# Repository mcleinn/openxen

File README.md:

# openxen

Custom Hall-effect microtonal hex keyboard: five identical 56-key Lumatone-shaped modules with Wooting Lekker Tikken switches, one AT32F405 per module, analog key depth streamed to [xentool](https://github.com/mcleinn/xentool).

Successor of [freexen](https://github.com/mcleinn/freexen) (DIY printed switches, one Teensy) and of the Wooting/Exquis software-only approach.

- `PROJECT_PLAN.md` — the plan, decisions and gates (read this first)
- `docs/` — our documents (provenance, verification notes, user inputs)
- `layout/` — machine-readable module specification and the generators built on it
- `hardware/` — KiCad project for the module PCB (derived from HE60, GPL-3.0)
- `firmware/` — libhmk-derived firmware for the module (GPL-3.0)
- `host/` — notes for the xentool backend
- `case/` — deltas against the freexen case
- `reference/` — third-party clones, datasheets and photos; **not part of the repository** (see `.gitignore`)

Hardware and firmware derived from [peppapighs/HE60](https://github.com/peppapighs/HE60) and [peppapighs/libhmk](https://github.com/peppapighs/libhmk) are licensed GPL-3.0; see `docs/provenance.md` for pinned commits.

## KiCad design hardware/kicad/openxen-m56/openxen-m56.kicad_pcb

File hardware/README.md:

# hardware — module PCB (KiCad 9)

Derived from HE60 v2.1 (GPL-3.0). Everything here is generated from `layout/module.json`, `parts.json` and HE60's files by the scripts in `generators/`; regenerate rather than hand-edit until Phase 4 routing starts.

| Path | Content |
|---|---|
| `parts.json` | Every part with LCSC code, footprint, JLCPCB basic/extended status and the reason for the choice |
| `kicad/lib/openxen.pretty` | `SW_Lekker_1u`, `LED_RGB_1206R_MHT151RGBCT` |
| `kicad/lib/openxen.kicad_sym` | MT9102ET (pin-compatible with GH39FKSW) and AT32F405RxT7 symbols from HE60 |
| `kicad/openxen-m56/` | project, library tables, generated schematic |
| `generators/sexp.py`, `kicad_sch.py` | S-expression reader/writer and schematic helpers |
| `generators/gen_project.py` | symbol library + project files |
| `generators/gen_schematic.py` | the schematic (run after `gen_project.py`) |

Checks: `kicad-cli sch erc --severity-all` on the schematic (clean as of 2026-11-06, one library-version note on the crystal symbol).

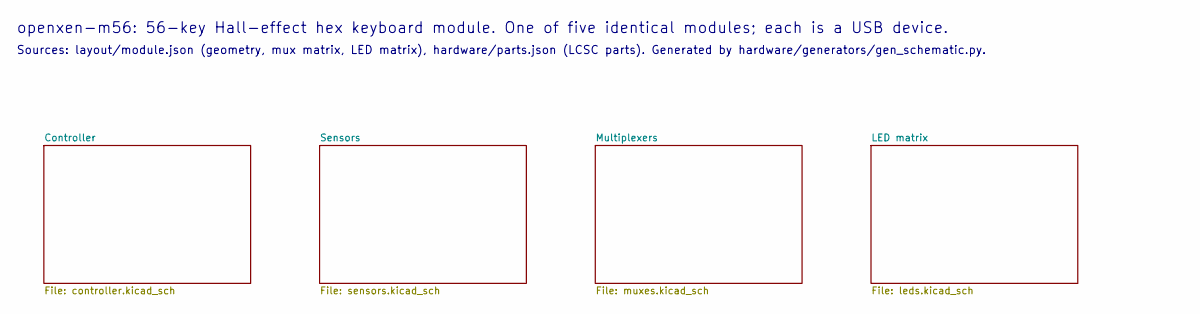
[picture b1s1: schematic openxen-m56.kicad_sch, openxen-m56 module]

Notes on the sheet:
openxen-m56: 56-key Hall-effect hex keyboard module. One of five identical modules; each is a USB device.
Sources: layout/module.json (geometry, mux matrix, LED matrix), hardware/parts.json (LCSC parts). Generated by hardware/generators/gen_schematic.py.

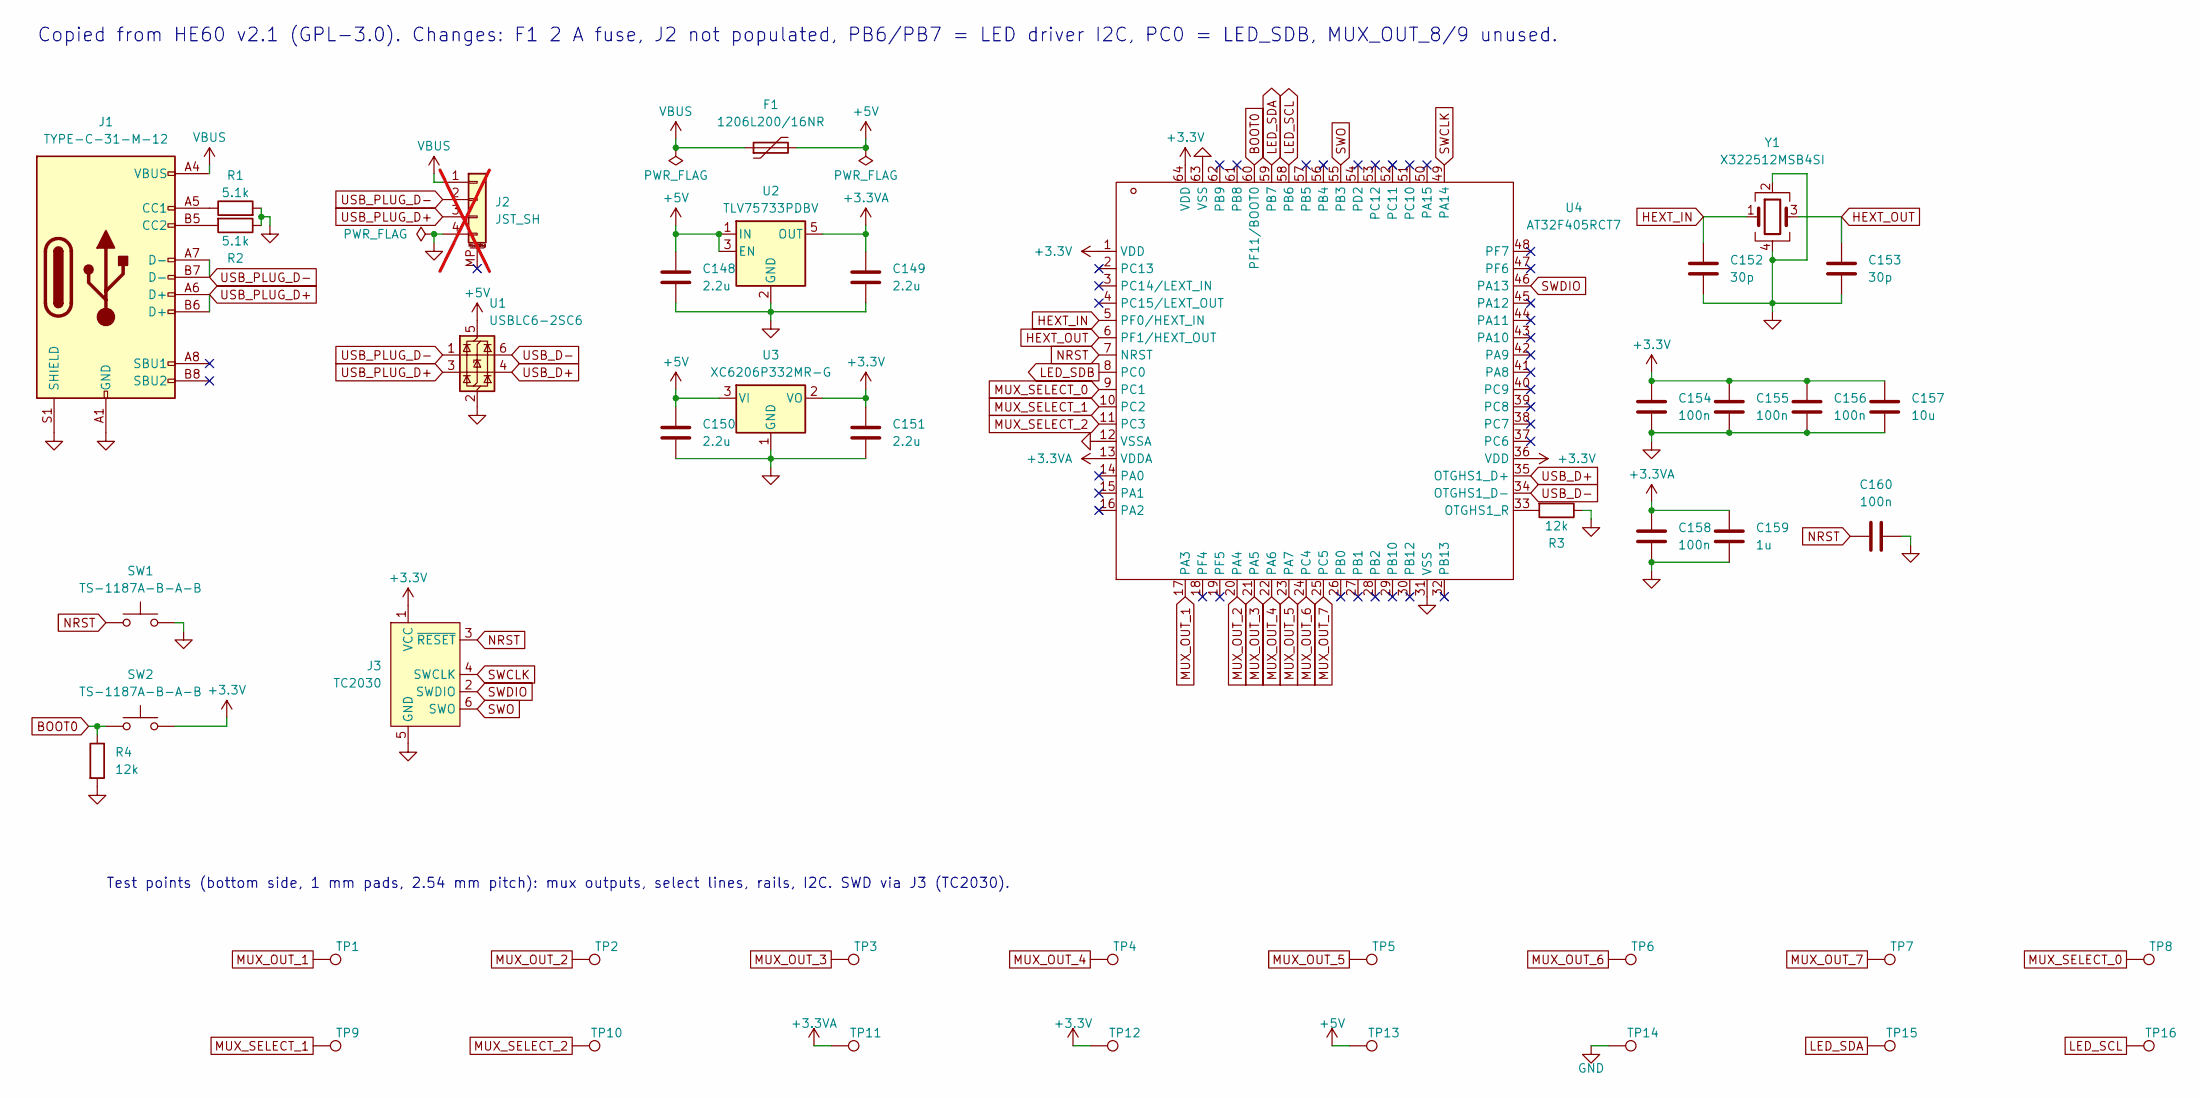
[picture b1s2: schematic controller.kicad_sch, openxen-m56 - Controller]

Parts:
C148, C149, C150, C151: 2.2u; C_0603_1608Metric; MPN CL10A225KO8NNNC; LCSC Part # C23630
C152, C153: 30p; C_0603_1608Metric; MPN 0603CG300J500NT; LCSC Part # C1658
C154, C155, C156, C158, C160: 100n; C_0402_1005Metric; MPN CL05B104KO5NNNC; LCSC Part # C1525
C157: 10u; C_0603_1608Metric; MPN CL10A106KP8NNNC; LCSC Part # C19702
C159: 1u; C_0603_1608Metric; MPN CL10A105KB8NNNC; LCSC Part # C15849
F1: 1206L200/16NR; Fuse_1206_3216Metric; MPN 1206L200/16NR; LCSC Part # C22374899
J1: TYPE-C-31-M-12; USB_C_Receptacle_HRO_TYPE-C-31-M-12; MPN TYPE-C-31-M-12; LCSC Part # C165948
J2: JST_SH; JST_SH_SM04B-SRSS-TB_1x04-1MP_P1.00mm_Horizontal; MPN SM04B-SRSS-TB(LF)(SN); LCSC Part # C160404; not fitted
J3: TC2030; Tag-Connect_TC2030-IDC-FP_2x03_P1.27mm_Vertical
R1, R2: 5.1k; R_0402_1005Metric; MPN 0402WGF5101TCE; LCSC Part # C25905
R3, R4: 12k; R_0402_1005Metric; MPN 0402WGF1202TCE; LCSC Part # C25752
SW1, SW2: TS-1187A-B-A-B; SW_Push_1P1T_XKB_TS-1187A; MPN TS-1187A-B-A-B; LCSC Part # C318884
TP1: MUX_OUT_1; TestPoint_Pad_D1.0mm
TP2: MUX_OUT_2; TestPoint_Pad_D1.0mm
TP3: MUX_OUT_3; TestPoint_Pad_D1.0mm
TP4: MUX_OUT_4; TestPoint_Pad_D1.0mm
TP5: MUX_OUT_5; TestPoint_Pad_D1.0mm
TP6: MUX_OUT_6; TestPoint_Pad_D1.0mm
TP7: MUX_OUT_7; TestPoint_Pad_D1.0mm
TP8: MUX_SELECT_0; TestPoint_Pad_D1.0mm
TP9: MUX_SELECT_1; TestPoint_Pad_D1.0mm
TP10: MUX_SELECT_2; TestPoint_Pad_D1.0mm
TP11: +3.3VA; TestPoint_Pad_D1.0mm
TP12: +3.3V; TestPoint_Pad_D1.0mm
TP13: +5V; TestPoint_Pad_D1.0mm
TP14: GND; TestPoint_Pad_D1.0mm
TP15: LED_SDA; TestPoint_Pad_D1.0mm
TP16: LED_SCL; TestPoint_Pad_D1.0mm
U1: USBLC6-2SC6; SOT-23-6; MPN USBLC6-2SC6; LCSC Part # C7519
U2: TLV75733PDBV; SOT-23-5; MPN TLV75733PDBVR; LCSC Part # C485517
U3: XC6206P332MR-G; SOT-23; MPN XC6206P332MR-G; LCSC Part # C5446
U4: AT32F405RCT7; LQFP-64_10x10mm_P0.5mm; MPN AT32F405RCT7; LCSC Part # C47090415
Y1: X322512MSB4SI; Crystal_SMD_3225-4Pin_3.2x2.5mm; MPN X322512MSB4SI; LCSC Part # C9002

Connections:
+3.3V: C151.1, C154.1, C155.1, C156.1, C157.1, J3.1 (VCC), SW2.2, TP12.1, U3.2 (VO), U4.1 (VDD), U4.36 (VDD), U4.64 (VDD); also elsewhere on the board
+3.3VA: C149.1, C158.1, C159.1, TP11.1, U2.5 (OUT), U4.13 (VDDA); also elsewhere on the board
+5V: C148.1, C150.1, F1.2, TP13.1, U1.5 (VBUS), U2.1 (IN), U2.3 (EN), U3.3 (VI); also elsewhere on the board
BOOT0: R4.1, SW2.1, U4.60 (PF11/BOOT0)
GND: C148.2, C149.2, C150.2, C151.2, C152.2, C153.2, C154.2, C155.2, C156.2, C157.2, C158.2, C159.2, C160.2, J1.A1 (GND), J1.A12 (GND), J1.B1 (GND), J1.B12 (GND), J1.S1 (SHIELD), J2.4, J3.5 (GND), R1.2, R2.1, R3.1, R4.2, SW1.2, TP14.1, U1.2 (GND), U2.2 (GND), U3.1 (GND), U4.12 (VSSA), U4.31 (VSS), U4.63 (VSS), Y1.2, Y1.4; also elsewhere on the board
HEXT_IN: C152.1, U4.5 (PF0/HEXT_IN), Y1.1
HEXT_OUT: C153.1, U4.6 (PF1/HEXT_OUT), Y1.3
LED_SCL: TP16.1, U4.58 (PB6); also elsewhere on the board
LED_SDA: TP15.1, U4.59 (PB7); also elsewhere on the board
LED_SDB: U4.8 (PC0); also elsewhere on the board
MUX_OUT_1: TP1.1, U4.17 (PA3); also elsewhere on the board
MUX_OUT_2: TP2.1, U4.20 (PA4); also elsewhere on the board
MUX_OUT_3: TP3.1, U4.21 (PA5); also elsewhere on the board
MUX_OUT_4: TP4.1, U4.22 (PA6); also elsewhere on the board
MUX_OUT_5: TP5.1, U4.23 (PA7); also elsewhere on the board
MUX_OUT_6: TP6.1, U4.24 (PC4); also elsewhere on the board
MUX_OUT_7: TP7.1, U4.25 (PC5); also elsewhere on the board
MUX_SELECT_0: TP8.1, U4.9 (PC1); also elsewhere on the board
MUX_SELECT_1: TP9.1, U4.10 (PC2); also elsewhere on the board
MUX_SELECT_2: TP10.1, U4.11 (PC3); also elsewhere on the board
NRST: C160.1, J3.3 (~RESET), SW1.1, U4.7 (NRST)
unnamed: J1.A5 (CC1), R1.1
unnamed: J1.B5 (CC2), R2.2
unnamed: R3.2, U4.33 (OTGHS1_R)
SWCLK: J3.4 (SWCLK), U4.49 (PA14)
SWDIO: J3.2 (SWDIO), U4.46 (PA13)
SWO: J3.6 (SWO), U4.55 (PB3)
USB_D+: U1.4 (I/O2), U4.35 (OTGHS1_D+)
USB_D-: U1.6 (I/O1), U4.34 (OTGHS1_D-)
USB_PLUG_D+: J1.A6 (D+), J1.B6 (D+), J2.3, U1.3 (I/O2)
USB_PLUG_D-: J1.A7 (D-), J1.B7 (D-), J2.2, U1.1 (I/O1)
VBUS: F1.1, J1.A4 (VBUS), J1.A9 (VBUS), J1.B4 (VBUS), J1.B9 (VBUS), J2.1

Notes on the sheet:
Copied from HE60 v2.1 (GPL-3.0). Changes: F1 2 A fuse, J2 not populated, PB6/PB7 = LED driver I2C, PC0 = LED_SDB, MUX_OUT_8/9 unused.
Test points (bottom side, 1 mm pads, 2.54 mm pitch): mux outputs, select lines, rails, I2C. SWD via J3 (TC2030).

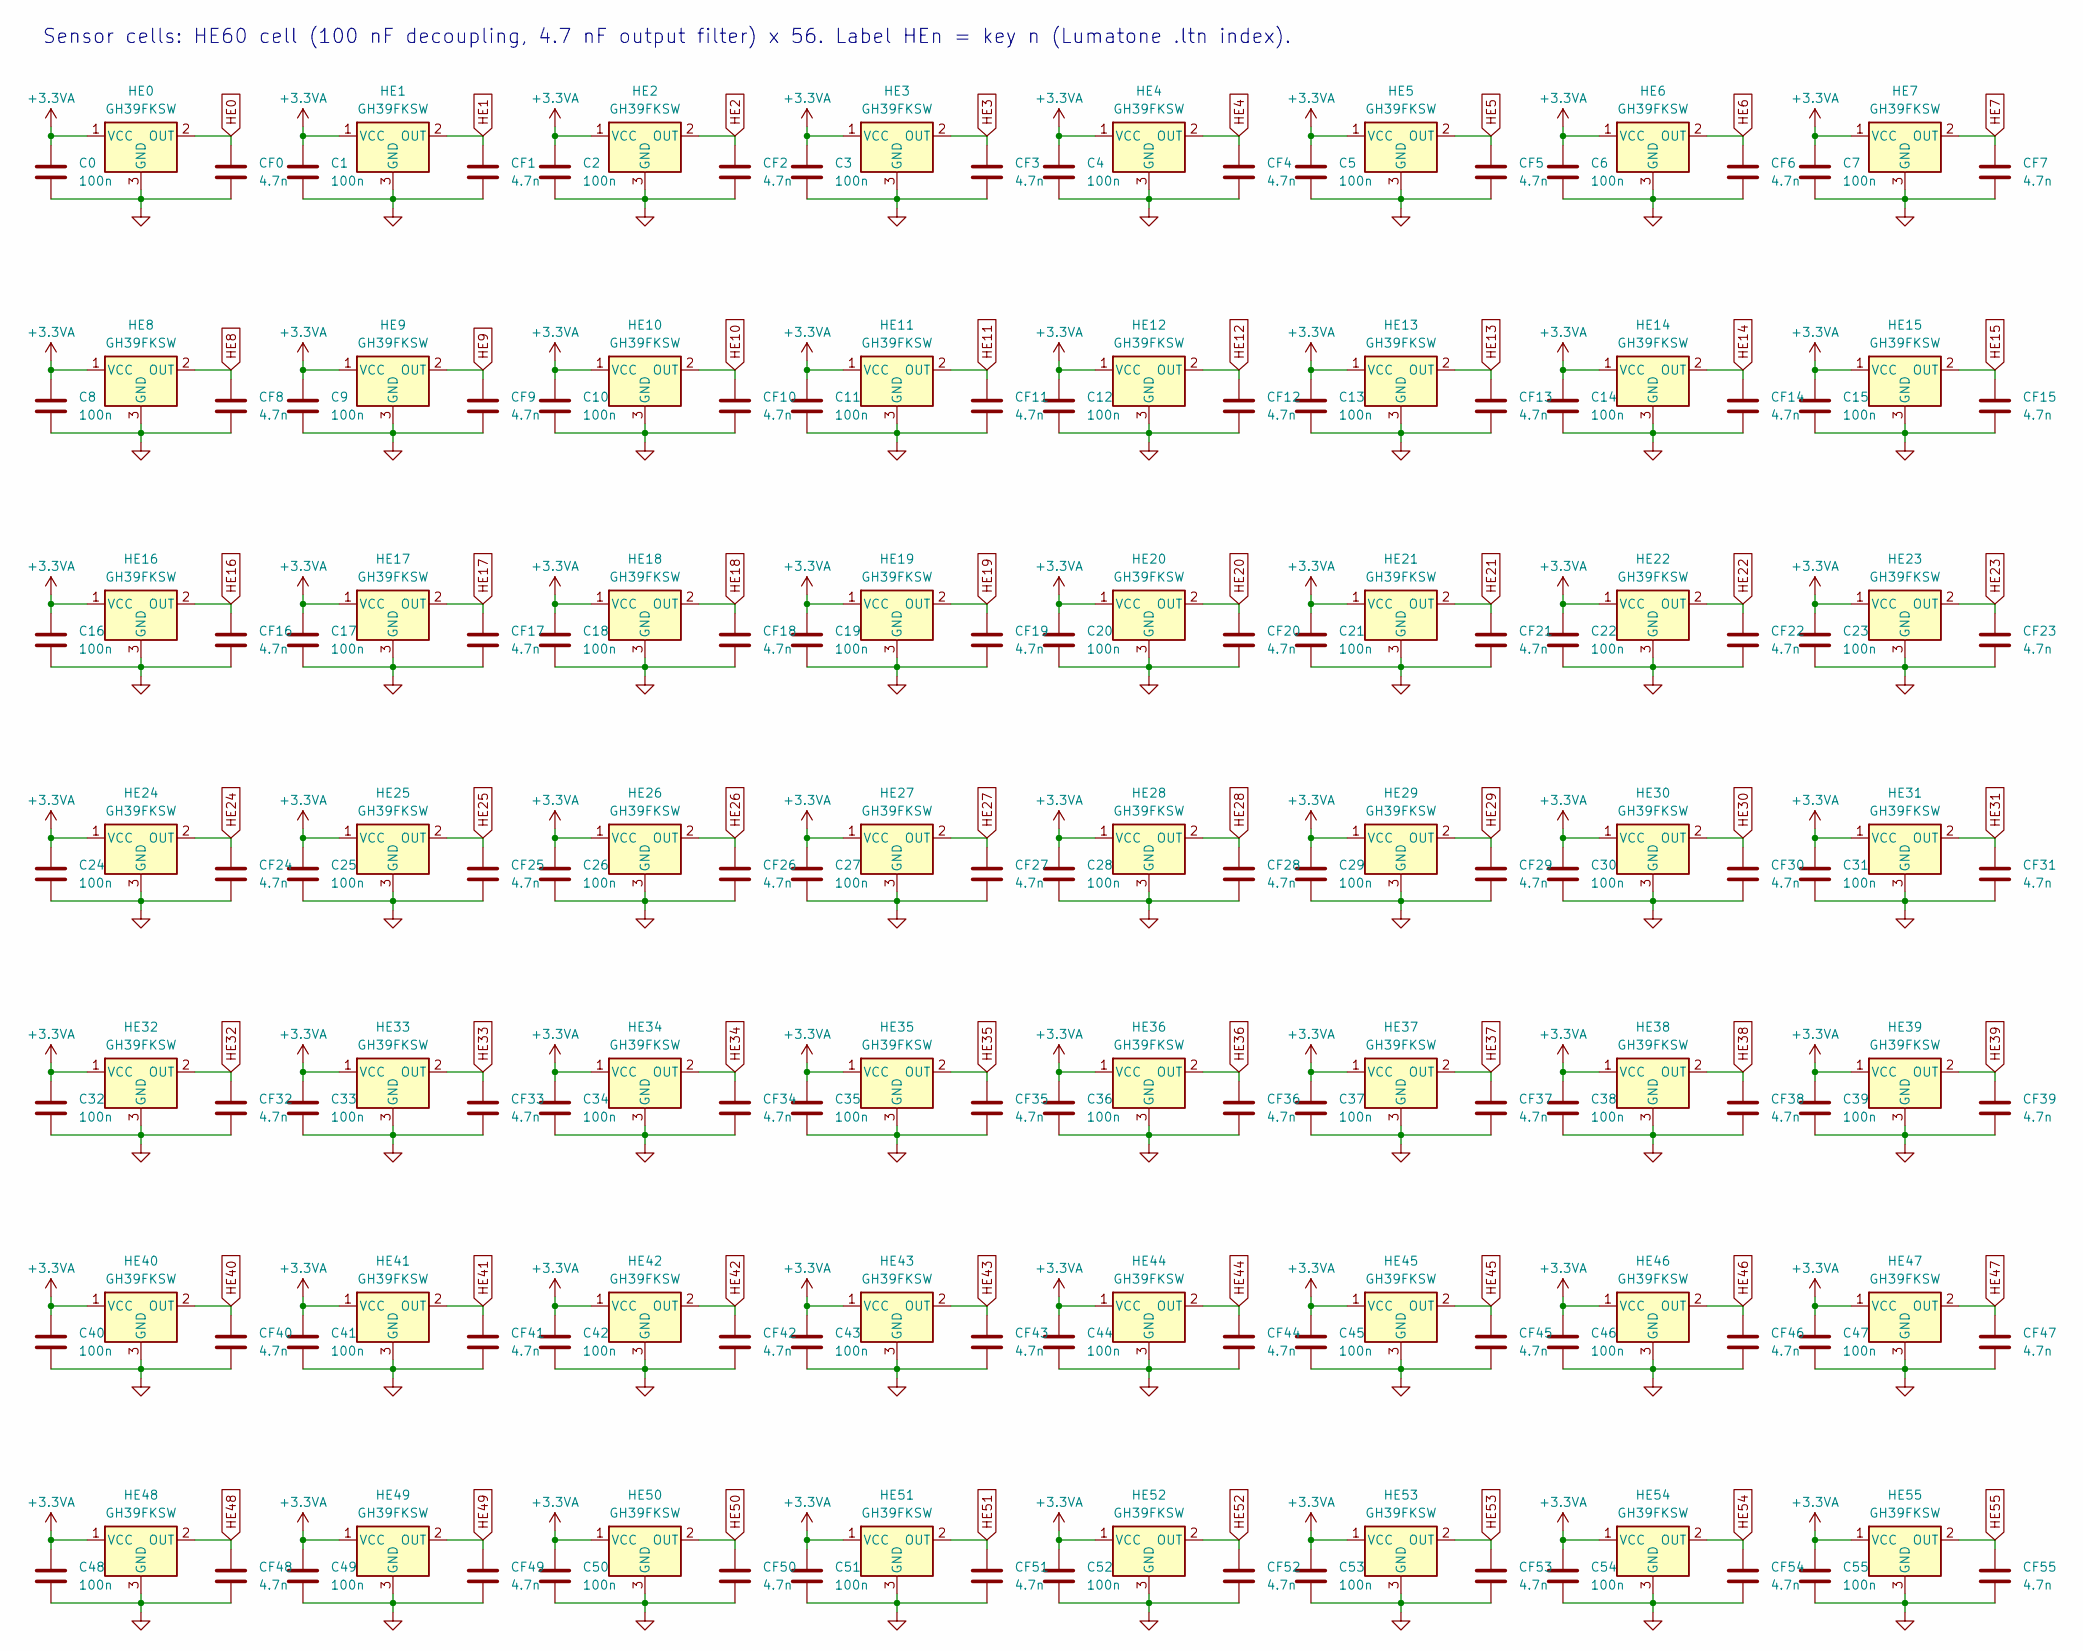
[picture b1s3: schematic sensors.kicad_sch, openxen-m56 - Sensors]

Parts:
C0, C1, C2, C3, C4, C5, C6, C7, C8, C9, C10, C11, C12, C13, C14, C15, C16, C17, C18, C19, C20, C21, C22, C23, C24, C25, C26, C27, C28, C29, C30, C31, C32, C33, C34, C35, C36, C37, C38, C39, C40, C41, C42, C43, C44, C45, C46, C47, C48, C49, C50, C51, C52, C53, C54, C55: 100n; C_0402_1005Metric; MPN CL05B104KO5NNNC; LCSC Part # C1525
CF0, CF1, CF2, CF3, CF4, CF5, CF6, CF7, CF8, CF9, CF10, CF11, CF12, CF13, CF14, CF15, CF16, CF17, CF18, CF19, CF20, CF21, CF22, CF23, CF24, CF25, CF26, CF27, CF28, CF29, CF30, CF31, CF32, CF33, CF34, CF35, CF36, CF37, CF38, CF39, CF40, CF41, CF42, CF43, CF44, CF45, CF46, CF47, CF48, CF49, CF50, CF51, CF52, CF53, CF54, CF55: 4.7n; C_0402_1005Metric; MPN 0402B472K500NT; LCSC Part # C1538
HE0, HE1, HE2, HE3, HE4, HE5, HE6, HE7, HE8, HE9, HE10, HE11, HE12, HE13, HE14, HE15, HE16, HE17, HE18, HE19, HE20, HE21, HE22, HE23, HE24, HE25, HE26, HE27, HE28, HE29, HE30, HE31, HE32, HE33, HE34, HE35, HE36, HE37, HE38, HE39, HE40, HE41, HE42, HE43, HE44, HE45, HE46, HE47, HE48, HE49, HE50, HE51, HE52, HE53, HE54, HE55: GH39FKSW; SOT-23; MPN GH39FKSW; LCSC Part # C266230

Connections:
+3.3VA: C0.1, C1.1, C2.1, C3.1, C4.1, C5.1, C6.1, C7.1, C8.1, C9.1, C10.1, C11.1, C12.1, C13.1, C14.1, C15.1, C16.1, C17.1, C18.1, C19.1, C20.1, C21.1, C22.1, C23.1, C24.1, C25.1, C26.1, C27.1, C28.1, C29.1, C30.1, C31.1, C32.1, C33.1, C34.1, C35.1, C36.1, C37.1, C38.1, C39.1, C40.1, C41.1, C42.1, C43.1, C44.1, C45.1, C46.1, C47.1, C48.1, C49.1, C50.1, C51.1, C52.1, C53.1, C54.1, C55.1, HE0.1 (VCC), HE1.1 (VCC), HE2.1 (VCC), HE3.1 (VCC), HE4.1 (VCC), HE5.1 (VCC), HE6.1 (VCC), HE7.1 (VCC), HE8.1 (VCC), HE9.1 (VCC), HE10.1 (VCC), HE11.1 (VCC), HE12.1 (VCC), HE13.1 (VCC), HE14.1 (VCC), HE15.1 (VCC), HE16.1 (VCC), HE17.1 (VCC), HE18.1 (VCC), HE19.1 (VCC), HE20.1 (VCC), HE21.1 (VCC), HE22.1 (VCC), HE23.1 (VCC), HE24.1 (VCC), HE25.1 (VCC), HE26.1 (VCC), HE27.1 (VCC), HE28.1 (VCC), HE29.1 (VCC), HE30.1 (VCC), HE31.1 (VCC), HE32.1 (VCC), HE33.1 (VCC), HE34.1 (VCC), HE35.1 (VCC), HE36.1 (VCC), HE37.1 (VCC), HE38.1 (VCC), HE39.1 (VCC), HE40.1 (VCC), HE41.1 (VCC), HE42.1 (VCC), HE43.1 (VCC), HE44.1 (VCC), HE45.1 (VCC), HE46.1 (VCC), HE47.1 (VCC), HE48.1 (VCC), HE49.1 (VCC), HE50.1 (VCC), HE51.1 (VCC), HE52.1 (VCC), HE53.1 (VCC), HE54.1 (VCC), HE55.1 (VCC); also elsewhere on the board
GND: C0.2, C1.2, C2.2, C3.2, C4.2, C5.2, C6.2, C7.2, C8.2, C9.2, C10.2, C11.2, C12.2, C13.2, C14.2, C15.2, C16.2, C17.2, C18.2, C19.2, C20.2, C21.2, C22.2, C23.2, C24.2, C25.2, C26.2, C27.2, C28.2, C29.2, C30.2, C31.2, C32.2, C33.2, C34.2, C35.2, C36.2, C37.2, C38.2, C39.2, C40.2, C41.2, C42.2, C43.2, C44.2, C45.2, C46.2, C47.2, C48.2, C49.2, C50.2, C51.2, C52.2, C53.2, C54.2, C55.2, CF0.2, CF1.2, CF2.2, CF3.2, CF4.2, CF5.2, CF6.2, CF7.2, CF8.2, CF9.2, CF10.2, CF11.2, CF12.2, CF13.2, CF14.2, CF15.2, CF16.2, CF17.2, CF18.2, CF19.2, CF20.2, CF21.2, CF22.2, CF23.2, CF24.2, CF25.2, CF26.2, CF27.2, CF28.2, CF29.2, CF30.2, CF31.2, CF32.2, CF33.2, CF34.2, CF35.2, CF36.2, CF37.2, CF38.2, CF39.2, CF40.2, CF41.2, CF42.2, CF43.2, CF44.2, CF45.2, CF46.2, CF47.2, CF48.2, CF49.2, CF50.2, CF51.2, CF52.2, CF53.2, CF54.2, CF55.2, HE0.3 (GND), HE1.3 (GND), HE2.3 (GND), HE3.3 (GND), HE4.3 (GND), HE5.3 (GND), HE6.3 (GND), HE7.3 (GND), HE8.3 (GND), HE9.3 (GND), HE10.3 (GND), HE11.3 (GND), HE12.3 (GND), HE13.3 (GND), HE14.3 (GND), HE15.3 (GND), HE16.3 (GND), HE17.3 (GND), HE18.3 (GND), HE19.3 (GND), HE20.3 (GND), HE21.3 (GND), HE22.3 (GND), HE23.3 (GND), HE24.3 (GND), HE25.3 (GND), HE26.3 (GND), HE27.3 (GND), HE28.3 (GND), HE29.3 (GND), HE30.3 (GND), HE31.3 (GND), HE32.3 (GND), HE33.3 (GND), HE34.3 (GND), HE35.3 (GND), HE36.3 (GND), HE37.3 (GND), HE38.3 (GND), HE39.3 (GND), HE40.3 (GND), HE41.3 (GND), HE42.3 (GND), HE43.3 (GND), HE44.3 (GND), HE45.3 (GND), HE46.3 (GND), HE47.3 (GND), HE48.3 (GND), HE49.3 (GND), HE50.3 (GND), HE51.3 (GND), HE52.3 (GND), HE53.3 (GND), HE54.3 (GND), HE55.3 (GND); also elsewhere on the board
HE0: CF0.1, HE0.2 (OUT); also elsewhere on the board
HE1: CF1.1, HE1.2 (OUT); also elsewhere on the board
HE2: CF2.1, HE2.2 (OUT); also elsewhere on the board
HE3: CF3.1, HE3.2 (OUT); also elsewhere on the board
HE4: CF4.1, HE4.2 (OUT); also elsewhere on the board
HE5: CF5.1, HE5.2 (OUT); also elsewhere on the board
HE6: CF6.1, HE6.2 (OUT); also elsewhere on the board
HE7: CF7.1, HE7.2 (OUT); also elsewhere on the board
HE8: CF8.1, HE8.2 (OUT); also elsewhere on the board
HE9: CF9.1, HE9.2 (OUT); also elsewhere on the board
HE10: CF10.1, HE10.2 (OUT); also elsewhere on the board
HE11: CF11.1, HE11.2 (OUT); also elsewhere on the board
HE12: CF12.1, HE12.2 (OUT); also elsewhere on the board
HE13: CF13.1, HE13.2 (OUT); also elsewhere on the board
HE14: CF14.1, HE14.2 (OUT); also elsewhere on the board
HE15: CF15.1, HE15.2 (OUT); also elsewhere on the board
HE16: CF16.1, HE16.2 (OUT); also elsewhere on the board
HE17: CF17.1, HE17.2 (OUT); also elsewhere on the board
HE18: CF18.1, HE18.2 (OUT); also elsewhere on the board
HE19: CF19.1, HE19.2 (OUT); also elsewhere on the board
HE20: CF20.1, HE20.2 (OUT); also elsewhere on the board
HE21: CF21.1, HE21.2 (OUT); also elsewhere on the board
HE22: CF22.1, HE22.2 (OUT); also elsewhere on the board
HE23: CF23.1, HE23.2 (OUT); also elsewhere on the board
HE24: CF24.1, HE24.2 (OUT); also elsewhere on the board
HE25: CF25.1, HE25.2 (OUT); also elsewhere on the board
HE26: CF26.1, HE26.2 (OUT); also elsewhere on the board
HE27: CF27.1, HE27.2 (OUT); also elsewhere on the board
HE28: CF28.1, HE28.2 (OUT); also elsewhere on the board
HE29: CF29.1, HE29.2 (OUT); also elsewhere on the board
HE30: CF30.1, HE30.2 (OUT); also elsewhere on the board
HE31: CF31.1, HE31.2 (OUT); also elsewhere on the board
HE32: CF32.1, HE32.2 (OUT); also elsewhere on the board
HE33: CF33.1, HE33.2 (OUT); also elsewhere on the board
HE34: CF34.1, HE34.2 (OUT); also elsewhere on the board
HE35: CF35.1, HE35.2 (OUT); also elsewhere on the board
HE36: CF36.1, HE36.2 (OUT); also elsewhere on the board
HE37: CF37.1, HE37.2 (OUT); also elsewhere on the board
HE38: CF38.1, HE38.2 (OUT); also elsewhere on the board
HE39: CF39.1, HE39.2 (OUT); also elsewhere on the board
HE40: CF40.1, HE40.2 (OUT); also elsewhere on the board
HE41: CF41.1, HE41.2 (OUT); also elsewhere on the board
HE42: CF42.1, HE42.2 (OUT); also elsewhere on the board
HE43: CF43.1, HE43.2 (OUT); also elsewhere on the board
HE44: CF44.1, HE44.2 (OUT); also elsewhere on the board
HE45: CF45.1, HE45.2 (OUT); also elsewhere on the board
HE46: CF46.1, HE46.2 (OUT); also elsewhere on the board
HE47: CF47.1, HE47.2 (OUT); also elsewhere on the board
HE48: CF48.1, HE48.2 (OUT); also elsewhere on the board
HE49: CF49.1, HE49.2 (OUT); also elsewhere on the board
HE50: CF50.1, HE50.2 (OUT); also elsewhere on the board
HE51: CF51.1, HE51.2 (OUT); also elsewhere on the board
HE52: CF52.1, HE52.2 (OUT); also elsewhere on the board
HE53: CF53.1, HE53.2 (OUT); also elsewhere on the board
HE54: CF54.1, HE54.2 (OUT); also elsewhere on the board
HE55: CF55.1, HE55.2 (OUT); also elsewhere on the board

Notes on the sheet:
Sensor cells: HE60 cell (100 nF decoupling, 4.7 nF output filter) x 56. Label HEn = key n (Lumatone .ltn index).

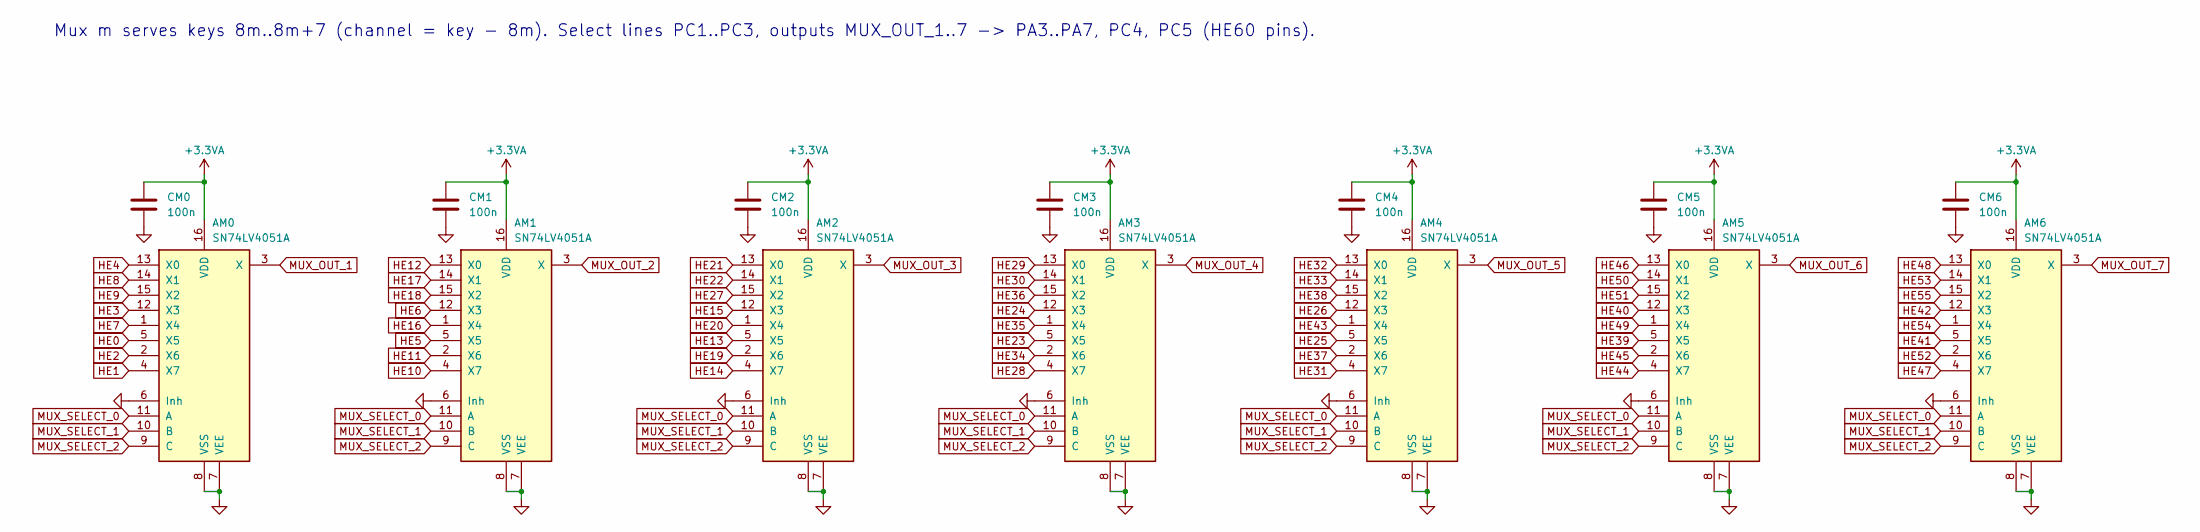
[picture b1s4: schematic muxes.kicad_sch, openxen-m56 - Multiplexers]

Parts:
AM0, AM1, AM2, AM3, AM4, AM5, AM6: SN74LV4051A; TSSOP-16_4.4x5mm_P0.65mm; MPN SN74LV4051APWR; LCSC Part # C7793
CM0, CM1, CM2, CM3, CM4, CM5, CM6: 100n; C_0402_1005Metric; MPN CL05B104KO5NNNC; LCSC Part # C1525

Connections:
+3.3VA: AM0.16 (VDD), AM1.16 (VDD), AM2.16 (VDD), AM3.16 (VDD), AM4.16 (VDD), AM5.16 (VDD), AM6.16 (VDD), CM0.1, CM1.1, CM2.1, CM3.1, CM4.1, CM5.1, CM6.1; also elsewhere on the board
GND: AM0.6 (Inh), AM0.7 (VEE), AM0.8 (VSS), AM1.6 (Inh), AM1.7 (VEE), AM1.8 (VSS), AM2.6 (Inh), AM2.7 (VEE), AM2.8 (VSS), AM3.6 (Inh), AM3.7 (VEE), AM3.8 (VSS), AM4.6 (Inh), AM4.7 (VEE), AM4.8 (VSS), AM5.6 (Inh), AM5.7 (VEE), AM5.8 (VSS), AM6.6 (Inh), AM6.7 (VEE), AM6.8 (VSS), CM0.2, CM1.2, CM2.2, CM3.2, CM4.2, CM5.2, CM6.2; also elsewhere on the board
HE0: AM0.5 (X5); also elsewhere on the board
HE1: AM0.4 (X7); also elsewhere on the board
HE2: AM0.2 (X6); also elsewhere on the board
HE3: AM0.12 (X3); also elsewhere on the board
HE4: AM0.13 (X0); also elsewhere on the board
HE5: AM1.5 (X5); also elsewhere on the board
HE6: AM1.12 (X3); also elsewhere on the board
HE7: AM0.1 (X4); also elsewhere on the board
HE8: AM0.14 (X1); also elsewhere on the board
HE9: AM0.15 (X2); also elsewhere on the board
HE10: AM1.4 (X7); also elsewhere on the board
HE11: AM1.2 (X6); also elsewhere on the board
HE12: AM1.13 (X0); also elsewhere on the board
HE13: AM2.5 (X5); also elsewhere on the board
HE14: AM2.4 (X7); also elsewhere on the board
HE15: AM2.12 (X3); also elsewhere on the board
HE16: AM1.1 (X4); also elsewhere on the board
HE17: AM1.14 (X1); also elsewhere on the board
HE18: AM1.15 (X2); also elsewhere on the board
HE19: AM2.2 (X6); also elsewhere on the board
HE20: AM2.1 (X4); also elsewhere on the board
HE21: AM2.13 (X0); also elsewhere on the board
HE22: AM2.14 (X1); also elsewhere on the board
HE23: AM3.5 (X5); also elsewhere on the board
HE24: AM3.12 (X3); also elsewhere on the board
HE25: AM4.5 (X5); also elsewhere on the board
HE26: AM4.12 (X3); also elsewhere on the board
HE27: AM2.15 (X2); also elsewhere on the board
HE28: AM3.4 (X7); also elsewhere on the board
HE29: AM3.13 (X0); also elsewhere on the board
HE30: AM3.14 (X1); also elsewhere on the board
HE31: AM4.4 (X7); also elsewhere on the board
HE32: AM4.13 (X0); also elsewhere on the board
HE33: AM4.14 (X1); also elsewhere on the board
HE34: AM3.2 (X6); also elsewhere on the board
HE35: AM3.1 (X4); also elsewhere on the board
HE36: AM3.15 (X2); also elsewhere on the board
HE37: AM4.2 (X6); also elsewhere on the board
HE38: AM4.15 (X2); also elsewhere on the board
HE39: AM5.5 (X5); also elsewhere on the board
HE40: AM5.12 (X3); also elsewhere on the board
HE41: AM6.5 (X5); also elsewhere on the board
HE42: AM6.12 (X3); also elsewhere on the board
HE43: AM4.1 (X4); also elsewhere on the board
HE44: AM5.4 (X7); also elsewhere on the board
HE45: AM5.2 (X6); also elsewhere on the board
HE46: AM5.13 (X0); also elsewhere on the board
HE47: AM6.4 (X7); also elsewhere on the board
HE48: AM6.13 (X0); also elsewhere on the board
HE49: AM5.1 (X4); also elsewhere on the board
HE50: AM5.14 (X1); also elsewhere on the board
HE51: AM5.15 (X2); also elsewhere on the board
HE52: AM6.2 (X6); also elsewhere on the board
HE53: AM6.14 (X1); also elsewhere on the board
HE54: AM6.1 (X4); also elsewhere on the board
HE55: AM6.15 (X2); also elsewhere on the board
MUX_OUT_1: AM0.3 (X); also elsewhere on the board
MUX_OUT_2: AM1.3 (X); also elsewhere on the board
MUX_OUT_3: AM2.3 (X); also elsewhere on the board
MUX_OUT_4: AM3.3 (X); also elsewhere on the board
MUX_OUT_5: AM4.3 (X); also elsewhere on the board
MUX_OUT_6: AM5.3 (X); also elsewhere on the board
MUX_OUT_7: AM6.3 (X); also elsewhere on the board
MUX_SELECT_0: AM0.11 (A), AM1.11 (A), AM2.11 (A), AM3.11 (A), AM4.11 (A), AM5.11 (A), AM6.11 (A); also elsewhere on the board
MUX_SELECT_1: AM0.10 (B), AM1.10 (B), AM2.10 (B), AM3.10 (B), AM4.10 (B), AM5.10 (B), AM6.10 (B); also elsewhere on the board
MUX_SELECT_2: AM0.9 (C), AM1.9 (C), AM2.9 (C), AM3.9 (C), AM4.9 (C), AM5.9 (C), AM6.9 (C); also elsewhere on the board

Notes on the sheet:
Mux m serves keys 8m..8m+7 (channel = key - 8m). Select lines PC1..PC3, outputs MUX_OUT_1..7 -> PA3..PA7, PC4, PC5 (HE60 pins).

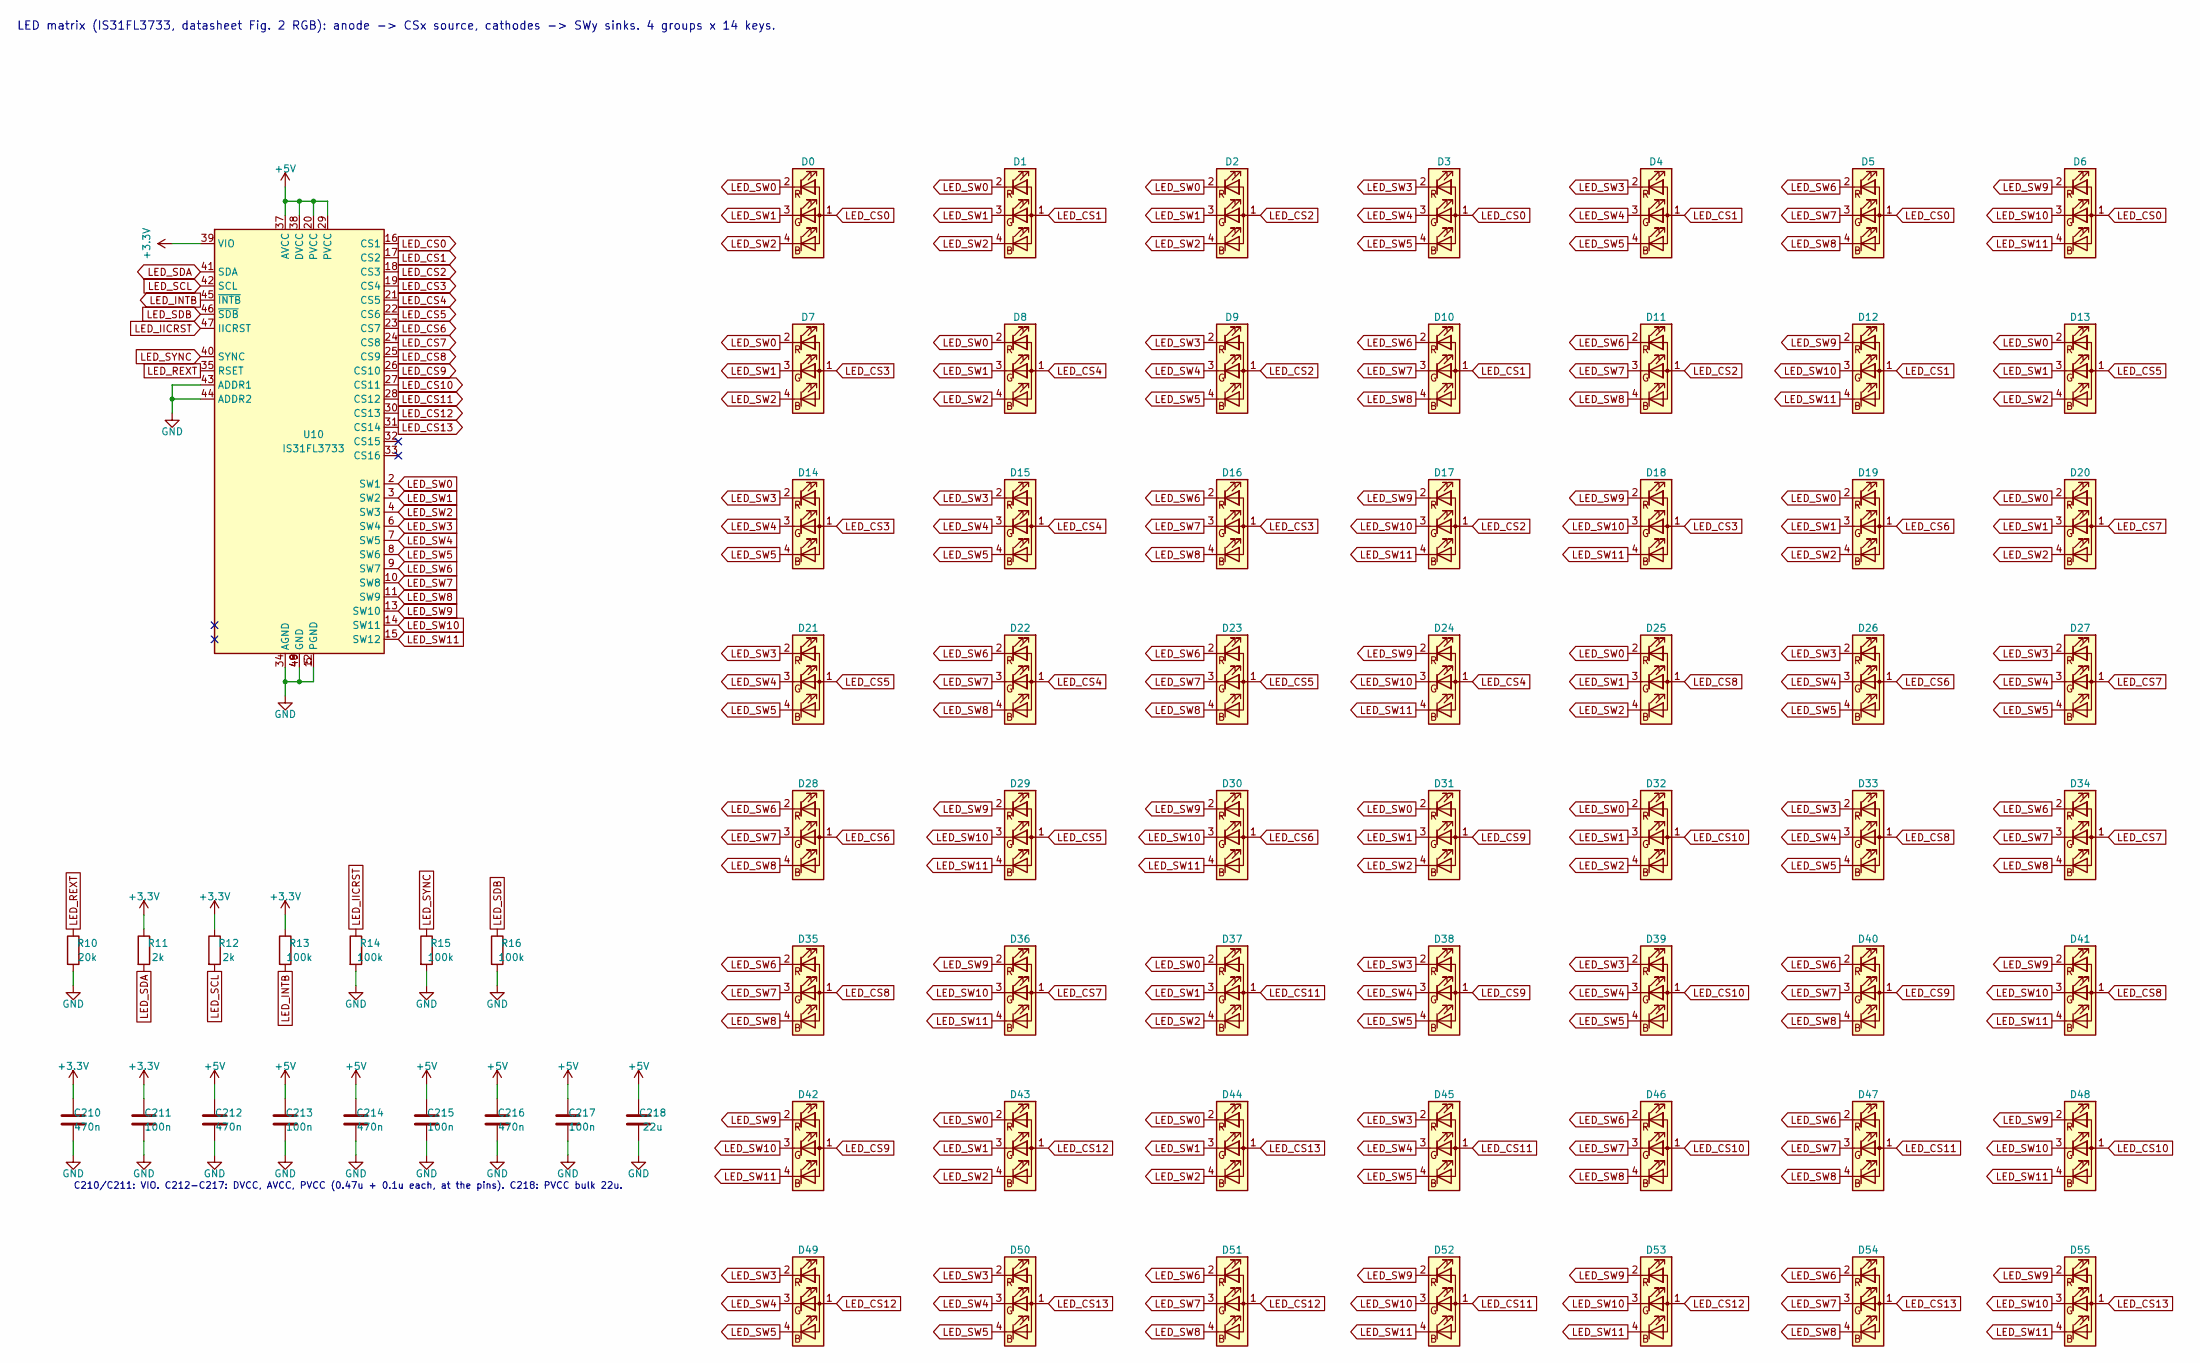
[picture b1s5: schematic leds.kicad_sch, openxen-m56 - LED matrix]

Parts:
C210, C212, C214, C216: 470n; C_0603_1608Metric; LCSC Part # C1623
C211, C213, C215, C217: 100n; C_0402_1005Metric; LCSC Part # C1525
C218: 22u; C_0805_2012Metric; LCSC Part # C45783
D0, D1, D2, D3, D4, D5, D6, D7, D8, D9, D10, D11, D12, D13, D14, D15, D16, D17, D18, D19, D20, D21, D22, D23, D24, D25, D26, D27, D28, D29, D30, D31, D32, D33, D34, D35, D36, D37, D38, D39, D40, D41, D42, D43, D44, D45, D46, D47, D48, D49, D50, D51, D52, D53, D54, D55: MHT151RGBCT; LED_RGB_1206R_MHT151RGBCT; LCSC Part # C409782
R10: 20k; R_0402_1005Metric; LCSC Part # C25765
R11, R12: 2k; R_0402_1005Metric; LCSC Part # C4109
R13, R14, R15, R16: 100k; R_0402_1005Metric; LCSC Part # C25741
U10: IS31FL3733; QFN-48-1EP_6x6mm_P0.4mm_EP4.2x4.2mm; MPN IS31FL3733-QFLS4-TR; LCSC Part # C506251

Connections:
+3.3V: C210.1, C211.1, R11.1, R12.1, R13.1, U10.39 (VIO); also elsewhere on the board
+5V: C212.1, C213.1, C214.1, C215.1, C216.1, C217.1, C218.1, U10.20 (PVCC), U10.29 (PVCC), U10.37 (AVCC), U10.38 (DVCC); also elsewhere on the board
GND: C210.2, C211.2, C212.2, C213.2, C214.2, C215.2, C216.2, C217.2, C218.2, R10.2, R14.2, R15.2, R16.2, U10.5 (PGND), U10.12 (PGND), U10.34 (AGND), U10.43 (ADDR1), U10.44 (ADDR2), U10.48 (GND), U10.49 (GND); also elsewhere on the board
LED_CS0: D0.1 (A), D3.1 (A), D5.1 (A), D6.1 (A), U10.16 (CS1)
LED_CS1: D1.1 (A), D4.1 (A), D10.1 (A), D12.1 (A), U10.17 (CS2)
LED_CS2: D2.1 (A), D9.1 (A), D11.1 (A), D17.1 (A), U10.18 (CS3)
LED_CS3: D7.1 (A), D14.1 (A), D16.1 (A), D18.1 (A), U10.19 (CS4)
LED_CS4: D8.1 (A), D15.1 (A), D22.1 (A), D24.1 (A), U10.21 (CS5)
LED_CS5: D13.1 (A), D21.1 (A), D23.1 (A), D29.1 (A), U10.22 (CS6)
LED_CS6: D19.1 (A), D26.1 (A), D28.1 (A), D30.1 (A), U10.23 (CS7)
LED_CS7: D20.1 (A), D27.1 (A), D34.1 (A), D36.1 (A), U10.24 (CS8)
LED_CS8: D25.1 (A), D33.1 (A), D35.1 (A), D41.1 (A), U10.25 (CS9)
LED_CS9: D31.1 (A), D38.1 (A), D40.1 (A), D42.1 (A), U10.26 (CS10)
LED_CS10: D32.1 (A), D39.1 (A), D46.1 (A), D48.1 (A), U10.27 (CS11)
LED_CS11: D37.1 (A), D45.1 (A), D47.1 (A), D52.1 (A), U10.28 (CS12)
LED_CS12: D43.1 (A), D49.1 (A), D51.1 (A), D53.1 (A), U10.30 (CS13)
LED_CS13: D44.1 (A), D50.1 (A), D54.1 (A), D55.1 (A), U10.31 (CS14)
LED_IICRST: R14.1, U10.47 (IICRST)
LED_INTB: R13.2, U10.45 (~INTB)
LED_REXT: R10.1, U10.35 (RSET)
LED_SCL: R12.2, U10.42 (SCL); also elsewhere on the board
LED_SDA: R11.2, U10.41 (SDA); also elsewhere on the board
LED_SDB: R16.1, U10.46 (~SDB); also elsewhere on the board
LED_SW0: D0.2 (RK), D1.2 (RK), D2.2 (RK), D7.2 (RK), D8.2 (RK), D13.2 (RK), D19.2 (RK), D20.2 (RK), D25.2 (RK), D31.2 (RK), D32.2 (RK), D37.2 (RK), D43.2 (RK), D44.2 (RK), U10.2 (SW1)
LED_SW1: D0.3 (GK), D1.3 (GK), D2.3 (GK), D7.3 (GK), D8.3 (GK), D13.3 (GK), D19.3 (GK), D20.3 (GK), D25.3 (GK), D31.3 (GK), D32.3 (GK), D37.3 (GK), D43.3 (GK), D44.3 (GK), U10.3 (SW2)
LED_SW2: D0.4 (BK), D1.4 (BK), D2.4 (BK), D7.4 (BK), D8.4 (BK), D13.4 (BK), D19.4 (BK), D20.4 (BK), D25.4 (BK), D31.4 (BK), D32.4 (BK), D37.4 (BK), D43.4 (BK), D44.4 (BK), U10.4 (SW3)
LED_SW3: D3.2 (RK), D4.2 (RK), D9.2 (RK), D14.2 (RK), D15.2 (RK), D21.2 (RK), D26.2 (RK), D27.2 (RK), D33.2 (RK), D38.2 (RK), D39.2 (RK), D45.2 (RK), D49.2 (RK), D50.2 (RK), U10.6 (SW4)
LED_SW4: D3.3 (GK), D4.3 (GK), D9.3 (GK), D14.3 (GK), D15.3 (GK), D21.3 (GK), D26.3 (GK), D27.3 (GK), D33.3 (GK), D38.3 (GK), D39.3 (GK), D45.3 (GK), D49.3 (GK), D50.3 (GK), U10.7 (SW5)
LED_SW5: D3.4 (BK), D4.4 (BK), D9.4 (BK), D14.4 (BK), D15.4 (BK), D21.4 (BK), D26.4 (BK), D27.4 (BK), D33.4 (BK), D38.4 (BK), D39.4 (BK), D45.4 (BK), D49.4 (BK), D50.4 (BK), U10.8 (SW6)
LED_SW6: D5.2 (RK), D10.2 (RK), D11.2 (RK), D16.2 (RK), D22.2 (RK), D23.2 (RK), D28.2 (RK), D34.2 (RK), D35.2 (RK), D40.2 (RK), D46.2 (RK), D47.2 (RK), D51.2 (RK), D54.2 (RK), U10.9 (SW7)
LED_SW7: D5.3 (GK), D10.3 (GK), D11.3 (GK), D16.3 (GK), D22.3 (GK), D23.3 (GK), D28.3 (GK), D34.3 (GK), D35.3 (GK), D40.3 (GK), D46.3 (GK), D47.3 (GK), D51.3 (GK), D54.3 (GK), U10.10 (SW8)
LED_SW8: D5.4 (BK), D10.4 (BK), D11.4 (BK), D16.4 (BK), D22.4 (BK), D23.4 (BK), D28.4 (BK), D34.4 (BK), D35.4 (BK), D40.4 (BK), D46.4 (BK), D47.4 (BK), D51.4 (BK), D54.4 (BK), U10.11 (SW9)
LED_SW9: D6.2 (RK), D12.2 (RK), D17.2 (RK), D18.2 (RK), D24.2 (RK), D29.2 (RK), D30.2 (RK), D36.2 (RK), D41.2 (RK), D42.2 (RK), D48.2 (RK), D52.2 (RK), D53.2 (RK), D55.2 (RK), U10.13 (SW10)
LED_SW10: D6.3 (GK), D12.3 (GK), D17.3 (GK), D18.3 (GK), D24.3 (GK), D29.3 (GK), D30.3 (GK), D36.3 (GK), D41.3 (GK), D42.3 (GK), D48.3 (GK), D52.3 (GK), D53.3 (GK), D55.3 (GK), U10.14 (SW11)
LED_SW11: D6.4 (BK), D12.4 (BK), D17.4 (BK), D18.4 (BK), D24.4 (BK), D29.4 (BK), D30.4 (BK), D36.4 (BK), D41.4 (BK), D42.4 (BK), D48.4 (BK), D52.4 (BK), D53.4 (BK), D55.4 (BK), U10.15 (SW12)
LED_SYNC: R15.1, U10.40 (SYNC)

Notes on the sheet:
LED matrix (IS31FL3733, datasheet Fig. 2 RGB): anode -> CSx source, cathodes -> SWy sinks. 4 groups x 14 keys.
C210/C211: VIO. C212-C217: DVCC, AVCC, PVCC (0.47u + 0.1u each, at the pins). C218: PVCC bulk 22u.

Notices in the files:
hardware/generators/gen_schematic.py:
HE60's embedded symbols become ours (hardware/kicad/lib/openxen.kicad_sym, GPL-3.0, see provenance)
hardware/kicad/openxen-m56/controller.kicad_sch:
openxen (GPL-3.0)
